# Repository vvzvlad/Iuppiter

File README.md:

# Iuppiter
Iuppiter board doc

Сделать предзаказ платы: http://madrobots.ru/p/iupitter/

Официальная Wiki iuppiter: http://146.148.21.117/doku.php?id=start

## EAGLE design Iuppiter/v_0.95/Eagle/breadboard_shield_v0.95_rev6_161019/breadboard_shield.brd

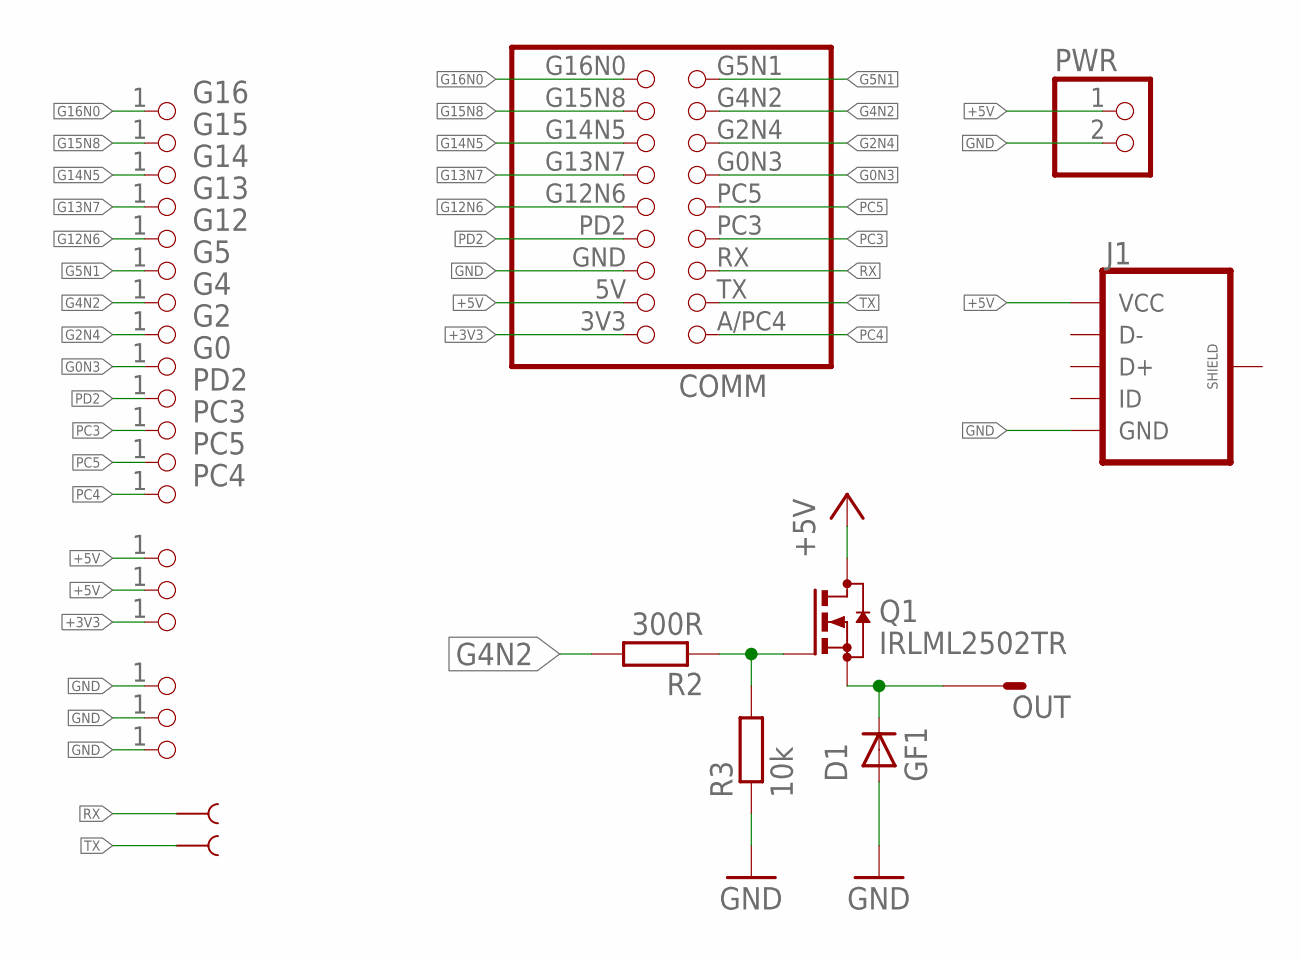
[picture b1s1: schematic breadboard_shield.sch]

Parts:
+3V, +5V: PINHD-1X1; 1X01
+5V1: +5V; 1X01
COMM: COMM_V2LEFT; COMM_V2_L(SHIELD)
D1: GF1; SMA-DO214AC
G0, G2, G4, G5, G12, G13, G14, G15, G16: PINHD-1X1; 1X01
GND: PINHD-1X1; 1X01
GND1, GND2: GND; 1X01
J1: USB_MICROB_PLUGCONN-11752; USB-B-MICRO-SMD_V03
OUT: M01PTH; 1X01
PC3, PC4, PC5: PINHD-1X1; 1X01
PD2: PINHD-1X1; 1X01
PWR: PINHD-1X2; 1X02
Q1: IRLML2502TR; SOT23
R2: 300R; R0805
R3: 10k; R0805
RX: TEST-POINT3X4; PAD.03X.04
TX: TEST-POINT3X4; PAD.03X.04

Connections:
+3V3: +3V.1, COMM.3V3 (+3V3)
+5V: +5V.1, +5V1.1, COMM.5V (+5), J1.VBUS (VCC), PWR.1, Q1.3 (D)
G0N3: COMM.G0N3, G0.1
G2N4: COMM.G2N4, G2.1
G4N2: COMM.G4N2, G4.1, R2.2
G5N1: COMM.G5N1, G5.1
G12N6: COMM.G12N6, G12.1
G13N7: COMM.G13N7, G13.1
G14N5: COMM.G14N5, G14.1
G15N8: COMM.G15N8, G15.1
G16N0: COMM.G16N0, G16.1
GND: COMM.GND, D1.A, GND.1, GND1.1, GND2.1, J1.GND, PWR.2, R3.1
unnamed: Q1.1 (G), R2.1, R3.2
OUT: D1.K (C), OUT.1, Q1.2 (S)
PC3: COMM.PC3, PC3.1
PC4: COMM.A/PC4 (ADC_PC4), PC4.1
PC5: COMM.PC5 (PC4), PC5.1
PD2: COMM.PD2, PD2.1
RX: COMM.RX, RX.P$1
TX: COMM.TX, TX.P$1

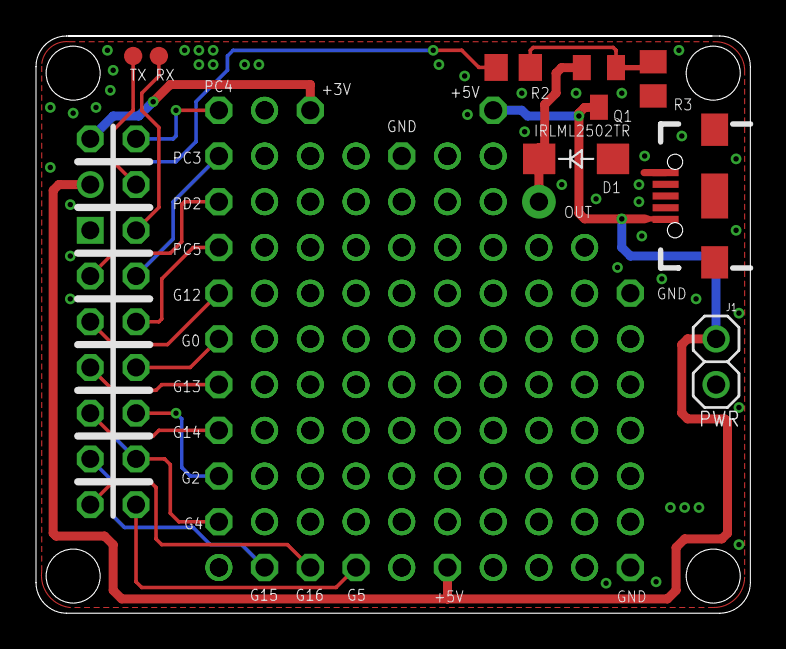
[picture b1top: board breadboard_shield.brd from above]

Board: 2 copper layers, 39.7 x 32.1 mm, 29 parts (0 on the bottom side), 20 nets.

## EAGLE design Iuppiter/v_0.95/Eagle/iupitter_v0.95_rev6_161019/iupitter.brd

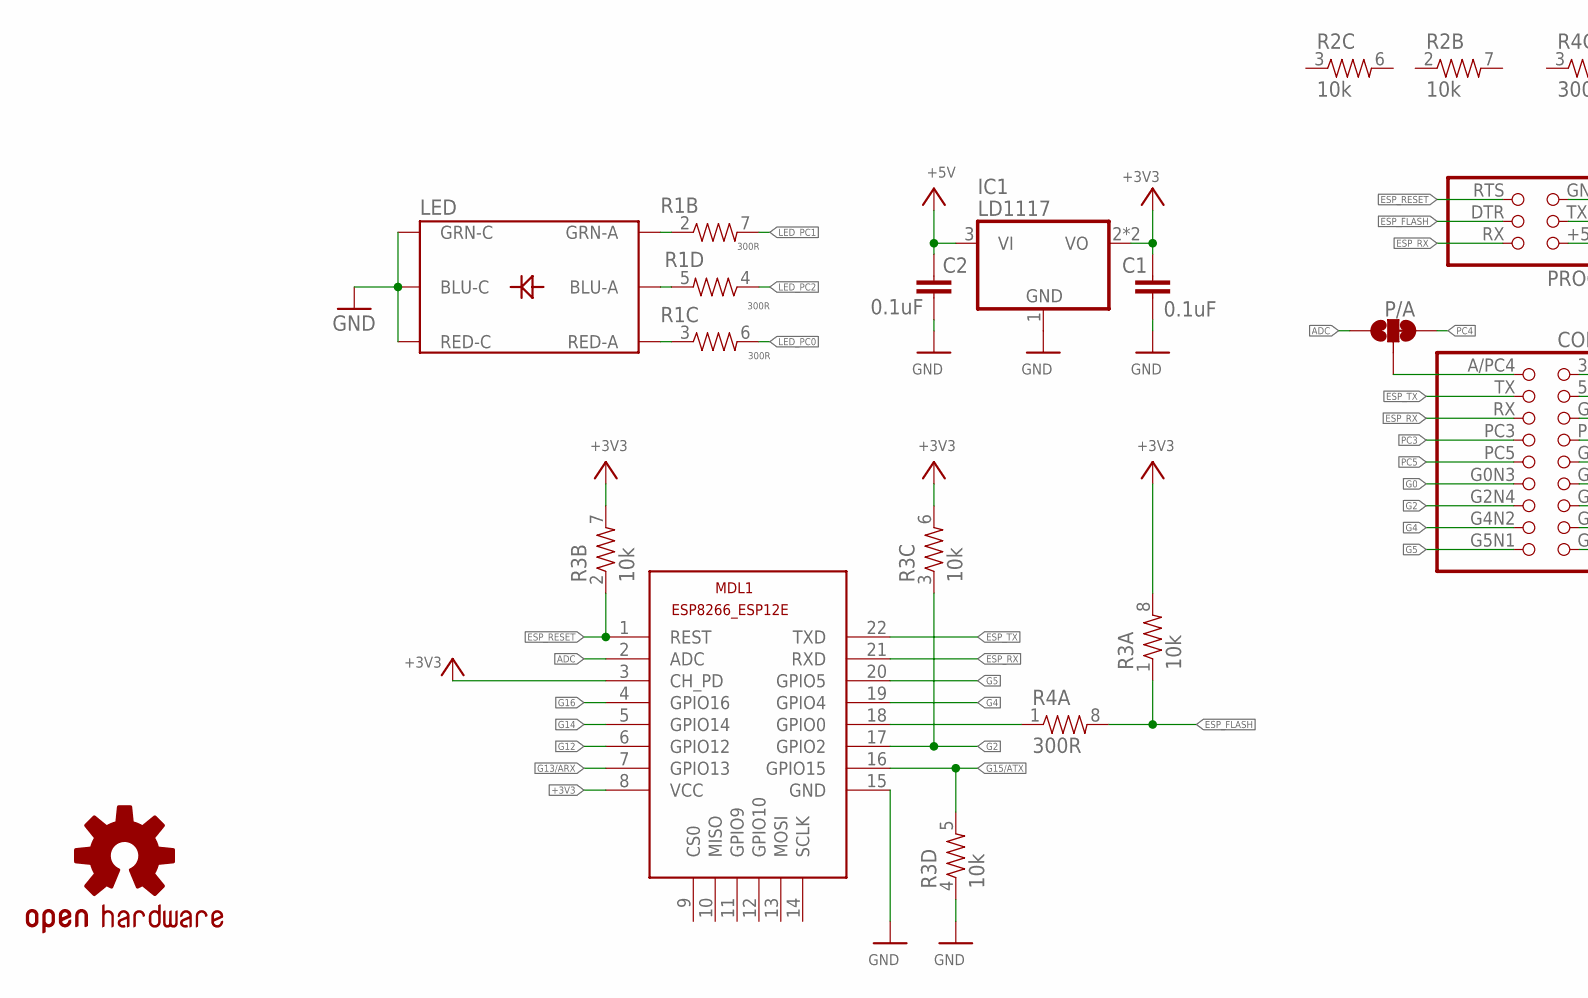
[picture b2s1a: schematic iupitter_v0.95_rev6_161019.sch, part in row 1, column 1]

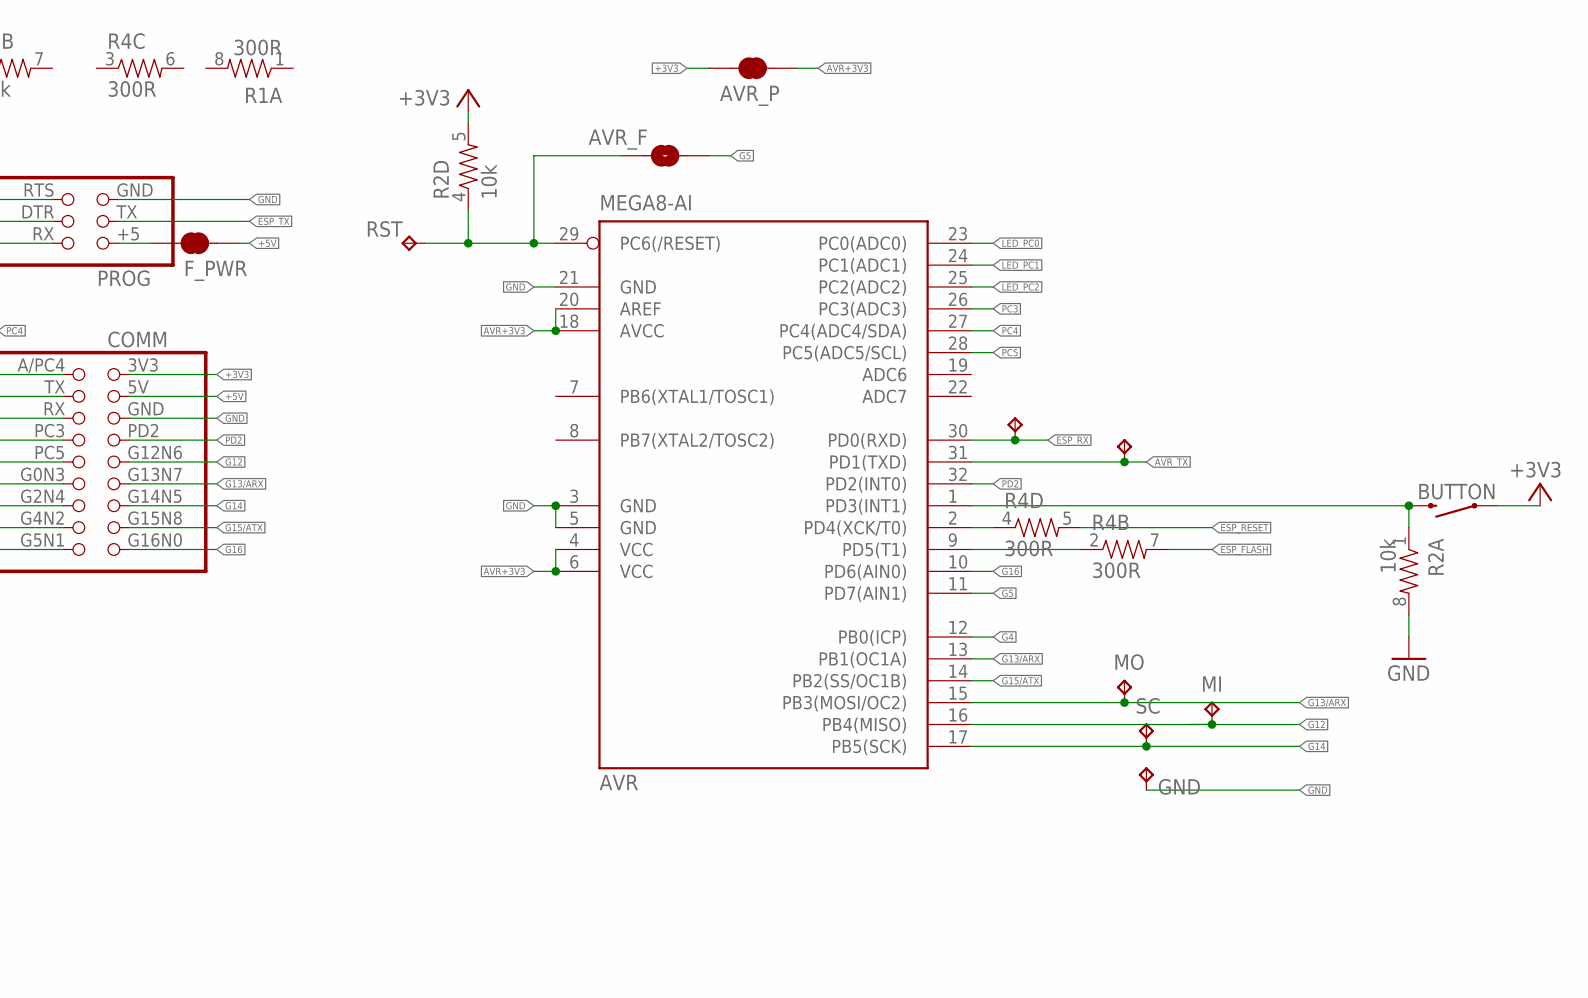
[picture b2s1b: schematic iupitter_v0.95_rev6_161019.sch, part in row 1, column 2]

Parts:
ARX: TPTP10SQ; TP10SQ
ATX: TPTP10SQ; TP10SQ
AVR: MEGA8-AI; TQFP32-08
AVR_F: JUMPER-PAD-2-NOYES_SILK; PAD-JUMPER-2-NO_YES_SILK
AVR_P: JUMPER-PAD-2-NC_BY_TRACE; PAD-JUMPER-2-NC_BY_TRACE_YES_SILK
BUTTON: IT-1181A; TACTILE-SWITCH-1101NE
C1, C2: 0.1uF; C1206
COMM: COMM_V2RIGHT; COMM_V2_R(MAIN)
F_PWR: JUMPER-PAD-2-NC_BY_TRACE; PAD-JUMPER-2-NC_BY_TRACE_YES_SILK
GND: TPTP10SQ; TP10SQ
IC1: LD1117; SOT223
LED: LED-TRICOLOR-5050NO_IC; LED-TRICOLOR-5050
LOGO1: OSHW-LOGOS-COPPER; OSHW-LOGO-S_COPPER
MDL1: ESP8266-12EESP8266-ESP12E; ESP8266-ESP12E
MI: TPTP10SQ; TP10SQ
MO: TPTP10SQ; TP10SQ
P/A: JUMPER-PAD-3-2OF3_NC_BY_TRACE_SMALL; PAD-JUMPER-3-2OF3_NC_BY_TRACE_YES_SILK_FULL_BOX
PROG: FLASH
R1, R4: 300R; 0603-ARV
R2, R3: 10k; 0603-ARV
RST: TPTP10SQ; TP10SQ
SC: TPTP10SQ; TP10SQ

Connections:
+3V3: AVR_P.1, BUTTON.1, C1.1, COMM.3V3 (+3V3), IC1.2 (VO), IC1.4 (VO), MDL1.3 (CH_PD), MDL1.8 (VCC), R2.5 (2), R3.6 (2), R3.7 (2), R3.8 (2)
+5V: C2.1, COMM.5V (+5), F_PWR.2, IC1.3 (VI)
ADC: MDL1.2 (ADC), P/A.1
AVR+3V3: AVR.4 (VCC), AVR.6 (VCC), AVR.18 (AVCC), AVR.20 (AREF), AVR_P.2
AVR_RESET: AVR.29 (PC6(/RESET)), AVR_F.1, R2.4 (1), RST.TP
AVR_TX: ATX.TP, AVR.31 (PD1(TXD))
BLUE_LED: LED.1 (BLU-A), R1.5 (2)
ESP_FLASH: PROG.DTR (4), R3.1, R4.7 (2), R4.8 (2)
ESP_RESET: MDL1.1 (REST), PROG.RTS (6), R3.2 (1), R4.5 (2)
ESP_RX: ARX.TP, AVR.30 (PD0(RXD)), COMM.RX, MDL1.21 (RXD), PROG.RX (2)
ESP_TX: COMM.TX, MDL1.22 (TXD), PROG.TX (3)
F+5V: F_PWR.1, PROG.+5 (1)
G0: COMM.G0N3, MDL1.18 (GPIO0), R4.1
G2: COMM.G2N4, MDL1.17 (GPIO2), R3.3 (1)
G4: AVR.12 (PB0(ICP)), COMM.G4N2, MDL1.19 (GPIO4)
G5: AVR.11 (PD7(AIN1)), AVR_F.2, COMM.G5N1, MDL1.20 (GPIO5)
G12: AVR.16 (PB4(MISO)), COMM.G12N6, MDL1.6 (GPIO12), MI.TP
G13/ARX: AVR.13 (PB1(OC1A)), AVR.15 (PB3(MOSI/OC2)), COMM.G13N7, MDL1.7 (GPIO13), MO.TP
G14: AVR.17 (PB5(SCK)), COMM.G14N5, MDL1.5 (GPIO14), SC.TP
G15/ATX: AVR.14 (PB2(SS/OC1B)), COMM.G15N8, MDL1.16 (GPIO15), R3.5 (2)
G16: AVR.10 (PD6(AIN0)), COMM.G16N0, MDL1.4 (GPIO16)
GND: AVR.3 (GND), AVR.5 (GND), AVR.21 (GND), C1.2, C2.2, COMM.GND, GND.TP, IC1.1 (GND), LED.4 (GRN-C), LED.5 (RED-C), LED.6 (BLU-C), MDL1.15 (GND), PROG.GND (5), R2.8 (2), R3.4 (1)
GREEN_LED: LED.3 (GRN-A), R1.2 (1)
LED_PC0: AVR.23 (PC0(ADC0)), R1.6 (2)
LED_PC1: AVR.24 (PC1(ADC1)), R1.7 (2)
LED_PC2: AVR.25 (PC2(ADC2)), R1.4 (1)
unnamed: COMM.A/PC4 (ADC_PC4), P/A.2
PC3: AVR.26 (PC3(ADC3)), COMM.PC3
PC4: AVR.27 (PC4(ADC4/SDA)), P/A.3
PC5: AVR.28 (PC5(ADC5/SCL)), COMM.PC5 (PC4)
PD2: AVR.32 (PD2(INT0)), COMM.PD2
PD3: AVR.1 (PD3(INT1)), BUTTON.2, R2.1
PD4: AVR.2 (PD4(XCK/T0)), R4.4 (1)
PD5: AVR.9 (PD5(T1)), R4.2 (1)
RED_LED: LED.2 (RED-A), R1.3 (1)

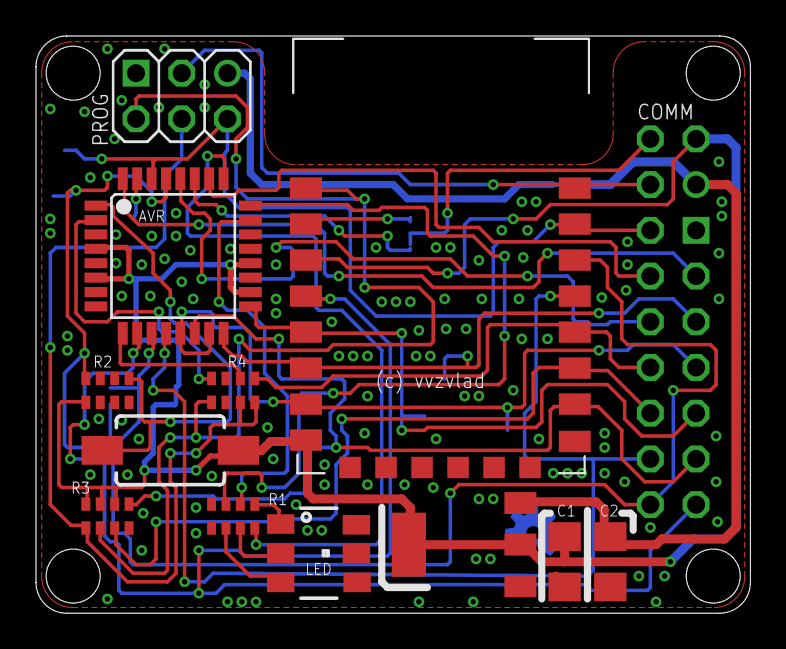
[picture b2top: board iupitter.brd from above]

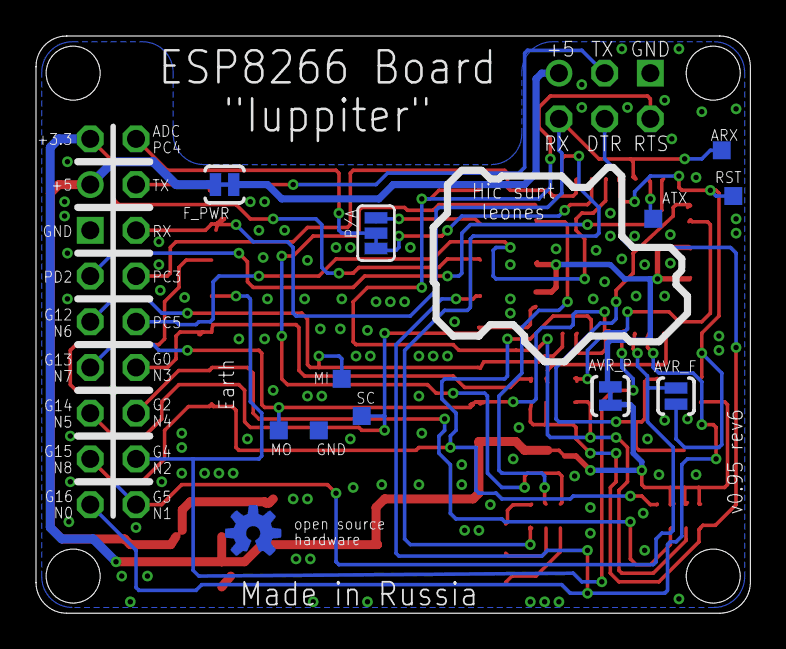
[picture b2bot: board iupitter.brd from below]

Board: 2 copper layers, 39.7 x 32.1 mm, 25 parts (12 on the bottom side), 35 nets.

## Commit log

2016-10-31 inital commit
2016-10-31 add gitignore
2016-10-31 add breadboard sch
2016-10-31 add default lua code
2016-10-31 edit default lua app
2016-11-01 add avrcore
2016-11-01 edit avrcore
2016-11-01 add sh tar and sha
2016-11-01 update avrcore
2016-11-01 avrcore update
2016-11-01 update avercore
2016-11-02 add esp8266 core
2016-11-02 update avr and esp core
2016-11-02 update core's
2016-11-02 update core esp
2016-11-02 update esp core
2016-11-02 update name cores
2016-11-02 del error
2016-11-02 update pic
2016-11-02 update gitignore
2016-11-02 update esp and avr core
2016-11-02 upd cores
2016-11-05 move breadboard eagle file
2016-11-05 move files
2016-11-05 add def nodemcu flash
2016-11-05 add avr programmer code for iuppiter
2016-11-05 update avrisp wifi
2016-11-05 add readme for standart nodemcu image
2016-11-05 update nodemcu image
2016-11-10 update default app

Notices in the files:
parts and their libraries:
SparkFun-Connectors: Licensing: Creative Commons ShareAlike 4.0 International - https://creativecommons.org/licenses/by-sa/4.0
